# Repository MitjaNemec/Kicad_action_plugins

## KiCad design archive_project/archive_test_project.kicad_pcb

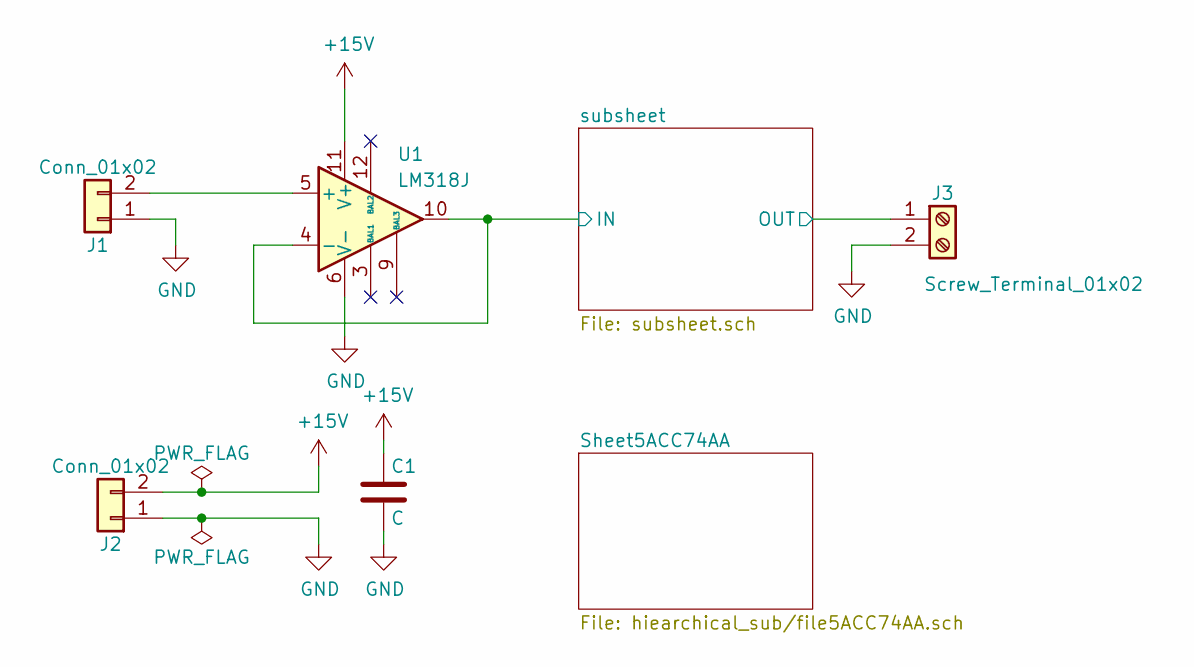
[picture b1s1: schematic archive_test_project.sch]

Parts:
C1: C; C_1206_3216Metric
J1, J2: Conn_01x02; PinHeader_1x02_P2.54mm_Horizontal
J3: Screw_Terminal_01x02; PhoenixContact_MSTBA_2,5_2-G-5,08_1x02_P5.08mm_Horizontal
U1: LM318J; DIP-14_W7.62mm

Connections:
+15V: C1.1, J2.2, U1.11 (V+)
/subsheet/IN: U1.4 (-), U1.10; also elsewhere on the board
/subsheet/OUT: J3.1; also elsewhere on the board
GND: C1.2, J1.1, J2.1, J3.2, U1.6 (V-); also elsewhere on the board
unnamed: J1.2, U1.5 (+)

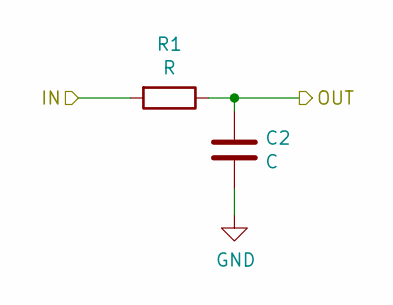
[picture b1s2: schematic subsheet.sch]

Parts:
C2: C; C_1206_3216Metric
R1: R; R_1206_3216Metric

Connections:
/subsheet/IN: R1.2; also elsewhere on the board
/subsheet/OUT: C2.1, R1.1; also elsewhere on the board
GND: C2.2; also elsewhere on the board

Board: 2 copper layers, 7 parts (0 on the bottom side), 5 nets, no tracks yet.

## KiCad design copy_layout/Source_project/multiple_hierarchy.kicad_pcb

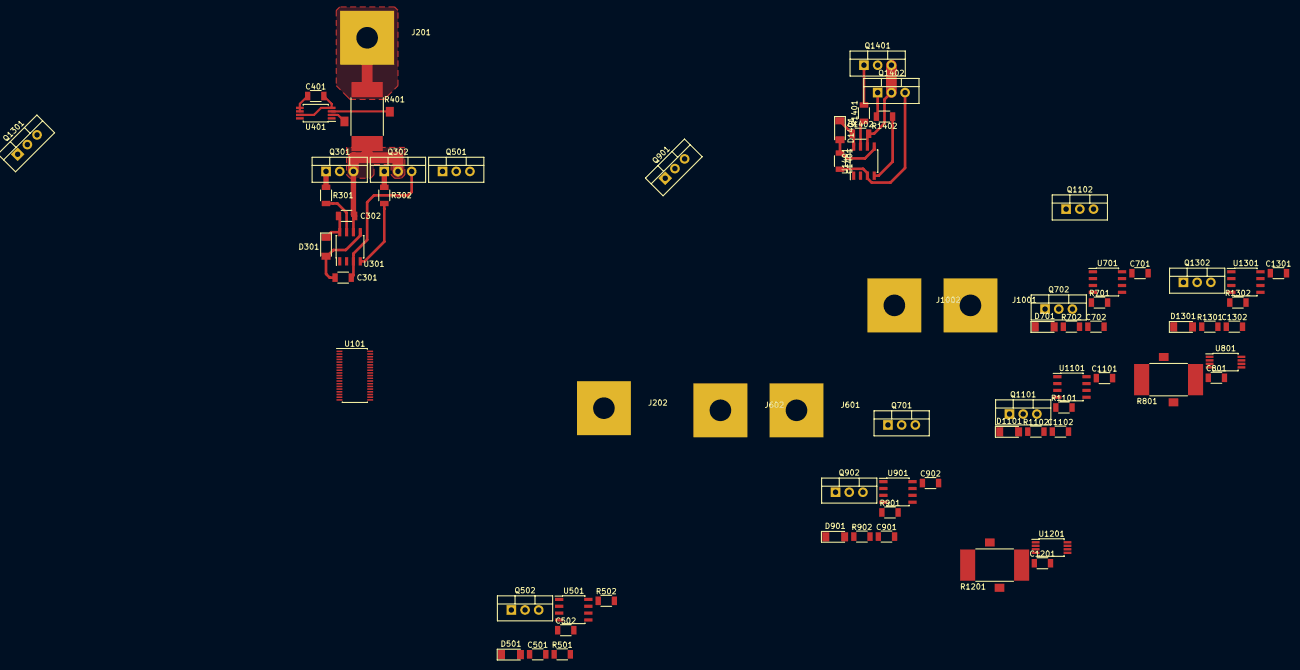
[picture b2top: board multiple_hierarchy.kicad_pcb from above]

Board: 2 copper layers, 72 parts (0 on the bottom side), 66 nets.

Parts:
C301, C302, C501, C502, C701, C702, C901, C902, C1101, C1102, C1301, C1302, C1401, C1402: 100n; C1206M
C401, C801, C1201: C1206; C1206M
D301, D501, D701, D901, D1101, D1301, D1401: LL4148; D_MiniMELF
J201, J202, J601, J602, J1001, J1002: Pusa_4mm
Q301, Q302, Q501, Q502, Q701, Q702, Q901, Q902, Q1101, Q1102, Q1301, Q1302, Q1401, Q1402: CSD19531KCS; TO-220
R301, R302, R501, R502, R701, R702, R901, R902, R1101, R1102, R1301, R1302, R1401, R1402: 22R; R1206M
R401, R801, R1201: R_Shunt; RM
U101: TMS320F28027DA; TSSOP-38_4.4x9.7mm_P0.5mm
U301, U501, U701, U901, U1101, U1301, U1401: IR2181; SO8
U401, U801, U1201: INA240; TSSOP-8_4.4x3mm_P0.65mm

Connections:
+3V3: C401.1, C801.1, C1201.1, U101.4, U101.22, U401.5, U401.6, U801.5, U801.6, U1201.5, U1201.6
+15V: C301.1, C501.1, C701.1, C901.1, C1101.1, C1301.1, C1401.1, D301.2, D501.2, D701.2, D901.2, D1101.2, D1301.2, D1401.2, U301.5, U501.5, U701.5, U901.5, U1101.5, U1301.5, U1401.5
+VDC: Q301.2, Q501.2, Q701.2, Q901.2, Q1101.2, Q1301.2, Q1401.2
-VDC: C301.2, C401.2, C501.2, C701.2, C801.2, C901.2, C1101.2, C1201.2, C1301.2, C1401.2, Q302.3, Q502.3, Q702.3, Q902.3, Q1102.3, Q1302.3, Q1402.3, U101.2, U101.12, U101.23, U301.3, U401.4, U401.7, U501.3, U701.3, U801.4, U801.7, U901.3, U1101.3, U1201.4, U1201.7, U1301.3, U1401.3
/Leg1/Current: U101.21, U401.8
/Leg1/Power-/OUT: C502.2, J202.1, Q501.3, Q502.2, U501.6
/Leg1/QH: U101.37, U301.1, U501.2
/Leg1/QL: U101.36, U301.2, U501.1
/Leg1/Sensor/IN: C302.2, Q301.3, Q302.2, R401.4, U301.6
/Leg1/Sensor/OUT: J201.1, R401.1
/Leg2/Current: U101.20, U801.8
/Leg2/Power-/OUT: C902.2, J602.1, Q901.3, Q902.2, U901.6
/Leg2/QH: U101.5, U701.1, U901.2
/Leg2/QL: U101.6, U701.2, U901.1
/Leg2/Sensor/IN: C702.2, Q701.3, Q702.2, R801.4, U701.6
/Leg2/Sensor/OUT: J601.1, R801.1
/Leg3/Current: U101.19, U1201.8
/Leg3/Power-/OUT: C1302.2, J1002.1, Q1301.3, Q1302.2, U1301.6
/Leg3/QH: U101.7, U1101.1, U1301.2
/Leg3/QL: U101.8, U1101.2, U1301.1
/Leg3/Sensor/IN: C1102.2, Q1101.3, Q1102.2, R1201.4, U1101.6
/Leg3/Sensor/OUT: J1001.1, R1201.1
/Power_extra/OUT: C1402.2, Q1401.3, Q1402.2, U1401.6
/Power_extra/QH: U101.9, U1401.1
/Power_extra/Ql: U101.10, U1401.2
unnamed: C302.1, D301.1, U301.8
unnamed: C502.1, D501.1, U501.8
unnamed: C702.1, D701.1, U701.8
unnamed: C902.1, D901.1, U901.8
unnamed: C1102.1, D1101.1, U1101.8
unnamed: C1302.1, D1301.1, U1301.8
unnamed: C1402.1, D1401.1, U1401.8
unnamed: Q301.1, R301.2
unnamed: Q302.1, R302.2
unnamed: Q501.1, R501.2
unnamed: Q502.1, R502.2
unnamed: Q701.1, R701.2
unnamed: Q702.1, R702.2
unnamed: Q901.1, R901.2
unnamed: Q902.1, R902.2
unnamed: Q1101.1, R1101.2
unnamed: Q1102.1, R1102.2
unnamed: Q1301.1, R1301.2
unnamed: Q1302.1, R1302.2
unnamed: Q1401.1, R1401.2
unnamed: Q1402.1, R1402.2
unnamed: R301.1, U301.7
unnamed: R302.1, U301.4
unnamed: R401.2, U401.3
unnamed: R401.3, U401.2
unnamed: R501.1, U501.7
unnamed: R502.1, U501.4
unnamed: R701.1, U701.7
unnamed: R702.1, U701.4
unnamed: R801.2, U801.3
unnamed: R801.3, U801.2
unnamed: R901.1, U901.7
unnamed: R902.1, U901.4
unnamed: R1101.1, U1101.7
unnamed: R1102.1, U1101.4
unnamed: R1201.2, U1201.3
unnamed: R1201.3, U1201.2
unnamed: R1301.1, U1301.7
unnamed: R1302.1, U1301.4
unnamed: R1401.1, U1401.7
unnamed: R1402.1, U1401.4

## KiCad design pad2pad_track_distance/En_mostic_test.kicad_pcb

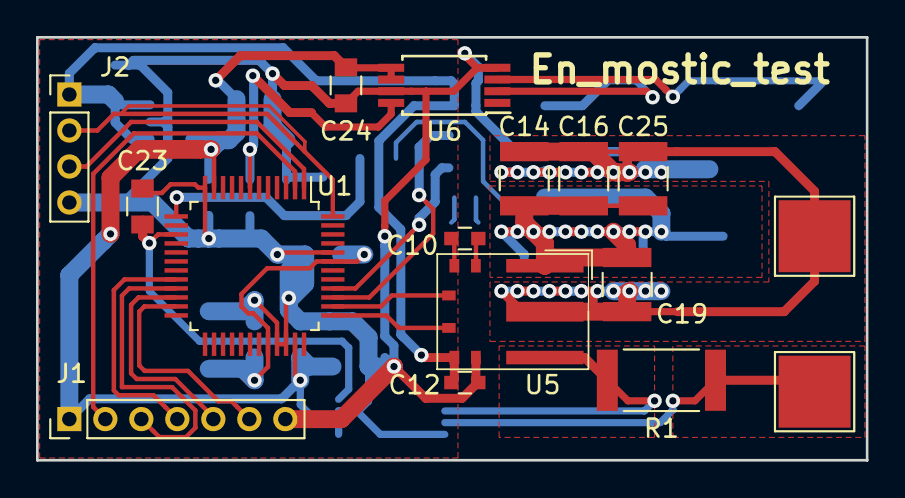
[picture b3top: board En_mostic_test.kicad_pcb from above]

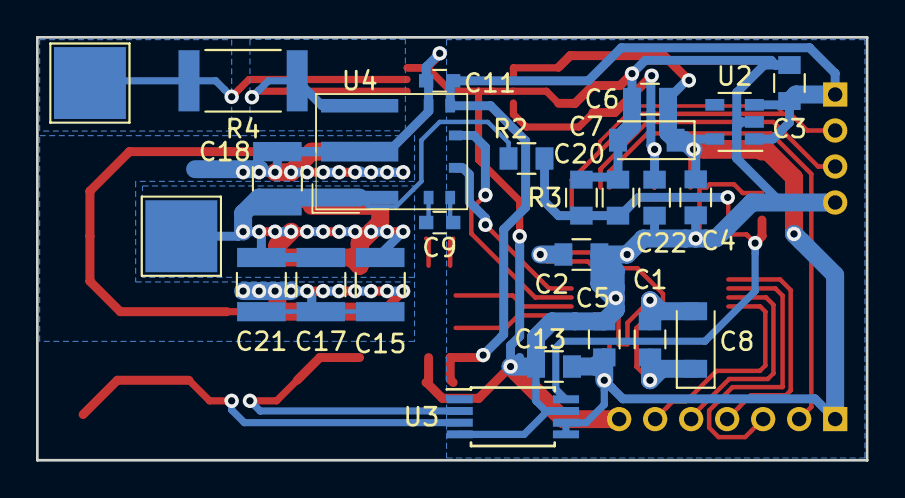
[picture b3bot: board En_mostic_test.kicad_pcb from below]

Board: 2 copper layers, 46.1 x 23.5 mm, 41 parts (25 on the bottom side), 27 nets.

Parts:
C1, C2, C3, C4, C5, C6, C13, C20, C24: 100nF; C0805M
C7, C8: 2u2; CT_A
C9, C10, C11, C12: 100nF; C0603M
C14, C15, C16, C17, C18, C19, C21, C25: 4u7; C_1210_3225Metric
C22, C23: 50pF; C0805M
J1: JTAG; PinHeader_1x07_P2.00mm_Vertical
J2: SCI; PinHeader_1x04_P2.00mm_Vertical
J3: M+; TestPoint_Pad_4.0x4.0mm
J4: M-; TestPoint_Pad_4.0x4.0mm
J5: DC+; TestPoint_Pad_4.0x4.0mm
J6: DC-; TestPoint_Pad_4.0x4.0mm
R1, R4: R; R_2512_6332Metric
R2: 100k; R0805M
R3: 10k; R0805M
U1: TMS320F28027PT; LQFP-48_7x7mm_P0.5mm
U2: TPS76333; SOT-23-5
U3, U6: INA240; TSSOP-8_4.4x3mm_P0.65mm
U4, U5: LMG5200; QFM(MOF)

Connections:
+1V8: C1.1, C2.1, C8.1, U1.32, U1.43
+3V3: C4.1, C5.1, C6.1, C7.1, C13.1, C24.1, J1.1, U1.11, U1.35, U2.5, U3.5, U3.6, U6.5, U6.6
+5V: C3.1, C11.1, C12.1, J2.1, U2.1, U2.3, U4.6, U5.6
+VDC: C14.1, C15.1, C16.1, C17.1, C18.1, C19.1, C21.1, C25.1, J5.1, R2.1, U4.1, U5.1
-VDC: C1.2, C2.2, C3.2, C4.2, C5.2, C6.2, C7.2, C8.2, C11.2, C12.2, C13.2, C14.2, C15.2, C16.2, C17.2, C18.2, C19.2, C20.2, C21.2, C22.2, C23.2, C24.2, C25.2, J1.7, J2.4, J6.1, R3.2, U1.12, U1.33, U1.34, U1.44, U2.2, U3.4, U3.7, U4.7, U4.9, U5.7, U5.9, U6.4, U6.7
/M+: J3.1, R4.1, U6.3
/M-: J4.1, R1.1, U3.3
/NAP: C20.1, R2.2, R3.1, U1.13
/Q1: U1.40, U4.4
/Q2: U1.39, U4.5
/Q3: U1.38, U5.4
/Q4: U1.37, U5.5
/TOK+: C22.1, U1.7, U6.8
/TOK-: C23.1, U1.15, U3.8
unnamed: C9.1, U4.2
unnamed: C9.2, U4.3
unnamed: C10.1, U5.2
unnamed: C10.2, U5.3
unnamed: J1.2, U1.2
unnamed: J1.3, U1.21
unnamed: J1.4, U1.20
unnamed: J1.5, U1.22
unnamed: J1.6, U1.23
unnamed: J2.2, U1.48
unnamed: J2.3, U1.1
unnamed: R1.2, U3.2, U5.8
unnamed: R4.2, U4.8, U6.2
